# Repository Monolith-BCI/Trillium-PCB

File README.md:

## Monolith

We're a group of teens working on creating a BCI PCB to start running our own experiments on noise filtering, signal processing speed, and data collection. Our board takes in electrode data from 8 electrodes, and outputs the data over SPI so that we can process it with a neural network.

## Setup

KiCad plugins that we highly suggest installing:

* [`espressif/kicad-libraries`](https://github.com/espressif/kicad-libraries): KiCad libraries for Espressif chips and modules

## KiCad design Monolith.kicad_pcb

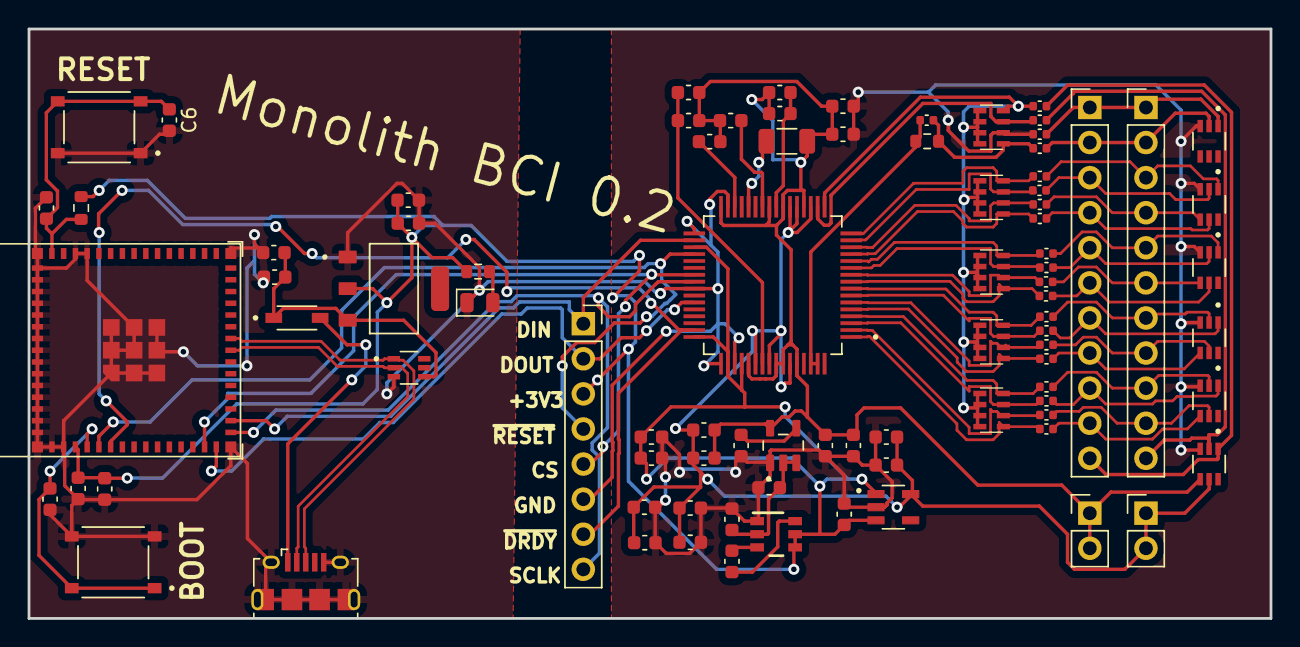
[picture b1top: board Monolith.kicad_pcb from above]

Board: 2 copper layers, 89.9 x 42.7 mm, 87 parts (0 on the bottom side), 67 nets.

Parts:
C1, C26, C27, C33, C45, C46, C53, C55: 10uF; C_0603_1608Metric
C2, C4, C6, C20, C32, C34, C41, C42, C48: 0.1uF; C_0603_1608Metric
C3, C35, C36, C37, C38, C39, C40, C43, C44: 1uF; C_0603_1608Metric
C19: 100uF; C_1206_3216Metric
C24, C25: 0.1uF/50V; C_0603_1608Metric
C47: .1uF; C_0603_1608Metric
C49, C50, C52, C54: C 2.2uF; C_0603_1608Metric
C51: C 0.1uF; C_0603_1608Metric
C56: 1nF; C_0402_1005Metric
D1, D2, D3, D4, D5, D6, D12: TPD4E1B06DCKR; TVS_TPD4E1B06DCKR
D10: 1N5819HW-7-F; SOD3715X145N
D11: EMERALD LED; LED_0805_2012Metric
J1: USB_B_Micro; USB_Micro-B_Amphenol_10118194_Horizontal
J2, J3: Conn_01x11; PinHeader_1x11_P2.54mm_Vertical
J4, J5: Conn_01x02; PinHeader_1x02_P2.54mm_Vertical
J7: Conn_01x08; PinSocket_1x08_P2.54mm_Vertical
R1, R2, R3, R4, R5, R7, R8, R9, R10, R11, R12, R13, R14, R15, R16, R18, R19, R20, R21, R29: R 2.2k; C_0402_1005Metric
R6: 10k; R_0603_1608Metric
R27: 100; R_0603_1608Metric
R28: 1M; R_0603_1608Metric
S1, S2: TS-1187A-B-A-B; SW_TS-1187A-B-A-B
U1: ADS1299IPAGR; QFP50P1200X1200X120-64N
U2: AMS1117-3.3; SOT229P700X180-4N
U4: LM2664M6; SOT95P280X145-6N
U5: TLV70025QDDCRQ1; SOT95P280X110-5N
U6: TPS72325; SOT95P280X145-5N
U7, U8, U9, U10, U11: CAP_CA0612_3P2X1P6_YAG
U12: ESP32-S3-MINI-1

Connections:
+3V3: C1.2, C2.2, C24.1, C27.1, C43.1, C47.1, C49.1, J7.3, R6.1, R27.1, U1.35 (~PWDN), U1.48 (DVDD), U1.50 (DVDD), U1.52 (CLKSEL), U2.2 (VO), U4.4 (~SD), U4.5 (V+), U5.1 (IN), U5.3 (EN), U12.3 (3V3)
/1N: D1.2, J2.3, R11.1
/1P: D1.1, J3.3, R5.1
/2N: D1.5, J2.4, R29.1
/2P: D1.4, J3.4, R16.1
/3N: D2.2, J2.5, R7.1
/3P: D2.1, J3.5, R1.1
/4N: D2.5, J2.6, R18.1
/4P: D2.4, J3.6, R12.1
/5N: D3.1, J2.7, R8.1
/5P: D3.2, J3.7, R2.1
/6N: D3.4, J2.8, R19.1
/6P: D3.5, J3.8, R13.1
/7N: D4.1, J2.9, R9.1
/7P: D4.2, J3.9, R3.1
/8N: D4.4, J2.10, R20.1
/8P: D4.5, J3.10, R14.1
/ADS Power/-RAW: C46.1, C50.1, U4.2 (OUT), U6.2 (IN), U6.3 (EN)
/AGND: D6.1, J2.1, J3.1, R15.1
/AVDD: C39.1, C40.1, C41.1, C42.1, C44.1, C48.1, C54.1, C55.1, D5.5, J4.1, J4.2, U1.19 (AVDD@1), U1.21 (AVDD@1), U1.22 (AVDD@1), U1.54 (AVDD1), U1.56 (AVDD@1), U1.59 (AVDD@2), U5.5 (OUT)
/AVSS: C19.2, C20.1, C32.1, C33.1, C34.1, C35.2, C36.1, C37.1, C38.1, C40.2, C42.2, C52.1, C53.1, D5.4, J5.1, J5.2, U1.20 (AVSS@1), U1.23 (AVSS@1), U1.25 (VREFN), U1.32 (AVSS@1), U1.53 (AVSS1), U1.57 (AVSS@1), U1.58 (AVSS@2), U1.60 (BIASREF), U6.5 (OUT)
/BIAS: D6.2, J2.2, J3.2, R21.1
/BIASOUT: C56.1, R28.2, U1.62 (BIASIN), U1.63 (BIASOUT)
/BIAS_DRV: C56.2, R21.2, R28.1, U11.5
/CS: J7.5, U1.39 (~CS), U12.14 (GPIO10/TOUCH10/ADC1_CH9/FSPICS0/FSPIIO4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)
/DIN: J7.1, U1.34 (DIN), U12.17 (GPIO13/TOUCH13/ADC2_CH2/FSPIQ/FSPIIO7/S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)
/DN: D12.2, J1.2 (D-), U12.23 (GPIO19/U1RTS/ADC2_CH8/CLK_OUT2/USB_D-)
/DOUT: J7.2, U1.43 (DOUT), U12.15 (GPIO11/TOUCH11/ADC2_CH0/FSPID/FSPIIO5/S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)
/DP: D12.1, J1.3 (D+), U12.24 (GPIO20/U1CTS/ADC2_CH9/CLK_OUT1/USB_D+)
/DRDY: J7.7, U1.47 (~DRDY), U12.6 (GPIO2/TOUCH2/ADC1_CH1)
/GPIO1: J7.4, U1.36 (~RESET), U12.5 (GPIO1/TOUCH1/ADC1_CH0)
/IN1N: R11.2, U1.15 (IN1N), U7.7
/IN1P: R5.2, U1.16 (IN1P), U7.8
/IN2N: R29.2, U1.13 (IN2N), U7.5
/IN2P: R16.2, U1.14 (IN2P), U7.6
/IN3N: R7.2, U1.11 (IN3N), U8.7
/IN3P: R1.2, U1.12 (IN3P), U8.8
/IN4N: R18.2, U1.9 (IN4N), U8.5
/IN4P: R12.2, U1.10 (IN4P), U8.6
/IN5N: R8.2, U1.7 (IN5N), U9.7
/IN5P: R2.2, U1.8 (IN5P), U9.8
/IN6N: R19.2, U1.5 (IN6N), U9.5
/IN6P: R13.2, U1.6 (IN6P), U9.6
/IN7N: R9.2, U1.3 (IN7N), U10.7
/IN7P: R3.2, U1.4 (IN7P), U10.8
/IN8N: R20.2, U1.1 (IN8N), U10.5
/IN8P: R14.2, U1.2 (IN8P), U10.6
/INSRB1: R4.2, U1.17 (SRB1), U7.1, U7.2, U7.3, U7.4, U8.1, U8.2, U8.3, U8.4, U9.1, U9.2, U9.3, U9.4, U10.1, U10.2, U10.3, U10.4, U11.1, U11.2, U11.3, U11.4, U11.8
/INSRB2: R10.2, U1.18 (SRB2), U11.7
/SCLK: J7.8, U1.40 (SCLK), U12.16 (GPIO12/TOUCH12/ADC2_CH1/FSPICLK/FSPIIO6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)
/SRB1: D5.1, J2.11, R4.1
/SRB2: D5.2, J3.11, R10.1
GND: C1.1, C2.1, C3.2, C4.1, C6.2, C24.2, C25.1, C26.1, C27.2, D11.1 (K), D12.3, J1.5 (GND), J1.6 (Shield), J7.6, S1.A, S1.B, S2.C, S2.D, U1.31 (RESV1), U1.33 (DGND), U1.41 (DAISY_IN), U1.49 (DGND), U1.51 (DGND), U2.1 (GND), U12.1 (GND), U12.2 (GND), U12.42 (GND), U12.43 (GND), U12.46 (GND), U12.47 (GND), U12.48 (GND), U12.49 (GND), U12.50 (GND), U12.51 (GND), U12.52 (GND), U12.53 (GND), U12.54 (GND), U12.55 (GND), U12.56 (GND), U12.57 (GND), U12.58 (GND), U12.59 (GND), U12.60 (GND), U12.61 (GND), U12.62 (GND), U12.63 (GND), U12.64 (GND), U12.65 (GND)
GNDA: C20.2, C38.2, C39.2, C41.2, C43.2, C44.2, C46.2, C47.2, C48.2, C49.2, C50.2, C51.2, C52.2, C53.2, C54.2, C55.2, D1.3, D2.3, D3.3, D4.3, D5.3, D6.3, R15.2, U4.1 (GND), U5.2 (GND), U6.1 (GND), U11.6
unnamed: D11.2 (A), R27.2
unnamed: C19.1, U1.28 (VCAP1)
unnamed: C37.2, U1.30 (VCAP2)
unnamed: C34.2, C35.1, U1.55 (VCAP3)
unnamed: C36.2, U1.26 (VCAP4)
unnamed: C32.2, C33.2, U1.24 (VREFP)
unnamed: C25.2, C26.2, D10.C, D12.4, U2.3 (VI)
unnamed: C45.1, U4.6 (CAP+)
unnamed: C45.2, U4.3 (CAP-)
unnamed: C51.1, U6.4 (NR)
unnamed: C3.1, C6.1, R6.2, S1.C, S1.D, U12.45 (EN)
unnamed: C4.2, S2.A, S2.B, U12.4 (GPIO0/BOOT)
VBUS: D10.A, J1.1 (VBUS)

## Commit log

2023-12-10 Clean up and commit
2023-12-10 fix shorted pin
2023-12-13 fix pick and place stuff
2023-12-13 fix capacitor array footprint
2023-12-13 fix usb
2023-12-28 Switch out ESP32 for correct model
2023-12-28 swap out esp
2023-12-28 add pin for SCLK on header
2023-12-28 Edit schematic
2023-12-28 stuff
2023-12-28 moar stuff
2023-12-28 fix led
2023-12-28 Replace volt reg
2023-12-28 fix vrm
2023-12-29 add ground planes
2023-12-29 fixes
2023-12-30 new fixes
2023-12-30 wahoo
2023-12-31 ready to fab?
2023-12-31 fix pin headers
2024-01-01 change text
2024-01-01 gerbers
2024-01-01 remove ref designators
2024-01-09 fix reset button
